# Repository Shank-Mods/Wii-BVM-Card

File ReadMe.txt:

These are the files I used to create the RVL-129X, a Wii on a BVM card. It is based on Martin's card. This project is essentially me craming his circuit into the corner, and adding pads to 1: solder the controller ports to and 2: bolt the Wii on. Consult his github for more info on the capabilities of the card portion of this project, as well as the software to program the Arduino.

Major Credits to Martin. Heres his github. He was awesome and super helpful. Could not have done this without him. Again, I just copied his homework and bolted a Wii to it. 
https://github.com/skumlos/bkm-129x-simple

It was a quick and dirty project not originally intended for public release. I am releaseing the files as is due to popular demand. It is cluttered, unoptimized, and made for my specific circumstances and my available parts. Sorry in advance.

Follow the Definitive Wii trimming gudie for information on how to trim and run the Wii. Standard trim. Run YPbPr and audio through shielded wire to the marked pads. SH is ground for shielding. Connect Controller lines to controller pads. 4 Layer Wii highly recommended. Leave the 1.8v LDO on the Wii. Ensure your Wii's settings have the resolution set to 480i if your PVMs are 15khz only. If your system is in 480p mode, you can disconnect the 3.3v-to-mode connection so set the system to composite and svideo mode, and run composite or luma to the Y line on the card for a usable black and white 15khz image that will let you navigate menus. 

The 129x card cannot pass audio through the slot, so audio comes out a 3.5mm jack and into the RCA jacks on the back. 

For voltage regulators, I purchased and bolted on an RVL-PSU. It contains all the voltage regulator rails the Wii needs. It is open source. You can assemble one yourself, use the open source design to integrate it onto this PCB, buy an RVL-PSU from CrazyGadget on the Bitbuilt forums, or design your own regulators if you are a pro. Do not use generic chinese voltage regulator boards, their power is not clean and will cause issues.

I included overkill voltage protection for every voltage rail of every controller port. This is because I plan to take it to Melee tournaments. The competitive Melee conroller modding scene has a huge problem with design and quality control of aftermarket and modded controllers. Many systems at tournaments have destroyed components caused by controllers overdrawing the voltage rails. These components are overkill, expensive, and tedious to solder. If these circumstances are not relevant to you, you can omit these components placed by the controller ports, and instead run 3.3v and 5v directly to the 3.3v and 5v pins of the controller ports with wires. 

Near the solder pads for the gamecube controller data wires are some diodes and filters. These are harvested from the lines connected to the data lines on the Wii motherboard. Diodes are for extra ESD protection. Filters can probably be jumpered over, but probably not best practice.

Resistors R2, R3, R4 and R5, along with R14, R15, R16 and R17 are not populated on this board. Csync pad is not used.

For screws I used the silver screws inside the wii, used mostly on the EMI shield.

For the fan and heatsink my usual setup: 35mm x 35mm x 7mm fan with 35mm x 35mm x 7mm heatsink, along with a 35x70mm copper plate. This setup has become the go-to in the portablizing community, and is used on many portables like the G-Wii. Use thermal paste between heatsink and copper plate. Use thermal pad between CPU/GPU and copper plate.

I didnt really plan where to put the USB port. I used a USB to micro SD card adapter, and mounted it to a GCC controller port with double sided foam adhesive tape. 

Theres an LDO (U5) that I didn't include on BOM because the replacement I purchased had a different pinout. I had to bodge it, but I added a jumper in case your LDO has that pinout. Check his github for specs on that part.

Included are 2 STLs that need to be printed. One is for mounting the Wii and the cooling system to the board. The other is the back plate. The back plate has 2 versions. V2 is the one I used. The extrusions for the screws are a little flimsy, so i made V3 to strengthen them. It should work and be stronger, but I never tested it so I included both. All 3d printed parts are mounted with silver scews from the Wii.

Order PCB with 1.6mm thickness. Its a 2 layer board, nothing special.

If you use this project, please credit me. Would love to see what people make with this. If you plan to monetize, please contact me.  

Troubleshooting tips I wish I knew:

Arduino must be programmed using the header. It WILL NOT WORK if programmed through the USB port on the arduino. 

Make sure U2 is being powered by U5 regulator. Different LDOs in that package have different pinouts. 

You can troubleshoot the signal chain by taking the Luma signal and skipping U2 and U1

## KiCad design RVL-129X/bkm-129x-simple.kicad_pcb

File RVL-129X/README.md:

A simplified version of the BKM-129X compatible board.

Should be able to be created at $25-30, with the ADG1611 being the most expensive component.

This requires an Arduino Nano v3 loaded with the latest BKM-129X-MCU code from https://github.com/skumlos/bkm-129x-mcu

For more information go to https://immerhax.com/?p=422

You are welcome to clone, produce and sell hardware based on this. Please keep changes and so on open source.

Cool kids give credit where due.

Thanks goes out to Nick Carney and Bob from RetroRGB for rigorious testing!

--------

Compatibility list and tested consoles (including issues):

PVM-9L2
- SNES (US region, CSYNC)
- Mega Drive 2 (EU region, 60 Hz modded with DFO for "true" 60 Hz, CSYNC)
- Master System 1 (EU region, 60 Hz modded with DFO for "true" 60 Hz, CSYNC)
- PC-Engine (White, with THS7374 external RGB amp, CSYNC)

BVM-D14
- Genesis 1 (60 Hz, CSYNC)

BVM-D9
- Nomad (60 Hz, Triple bypass modded, CSYNC)
- SNES (US region, CSYNC)
- Master System (60 Hz, sync issues like original 129X)
- TurboGrafx/PC-Engine (60 Hz, sync issues like original 129X)

---------

Board revision history:

D: Fix THS7374 filter bypass, move to Kicad 5

C: Rearranged some components for nicer layout

B: Added R29, R30, R31 to compensate for overbrightness

A: Changed R9 to 0 Ohm / jumper

---------

Copyright © 2020 Martin Hejnfelt <martin@hejnfelt.com>
This work is free. You can redistribute it and/or modify it under the
terms of the Do What The Fuck You Want To Public License, Version 2,
as published by Sam Hocevar. See the LICENSE file for more details.

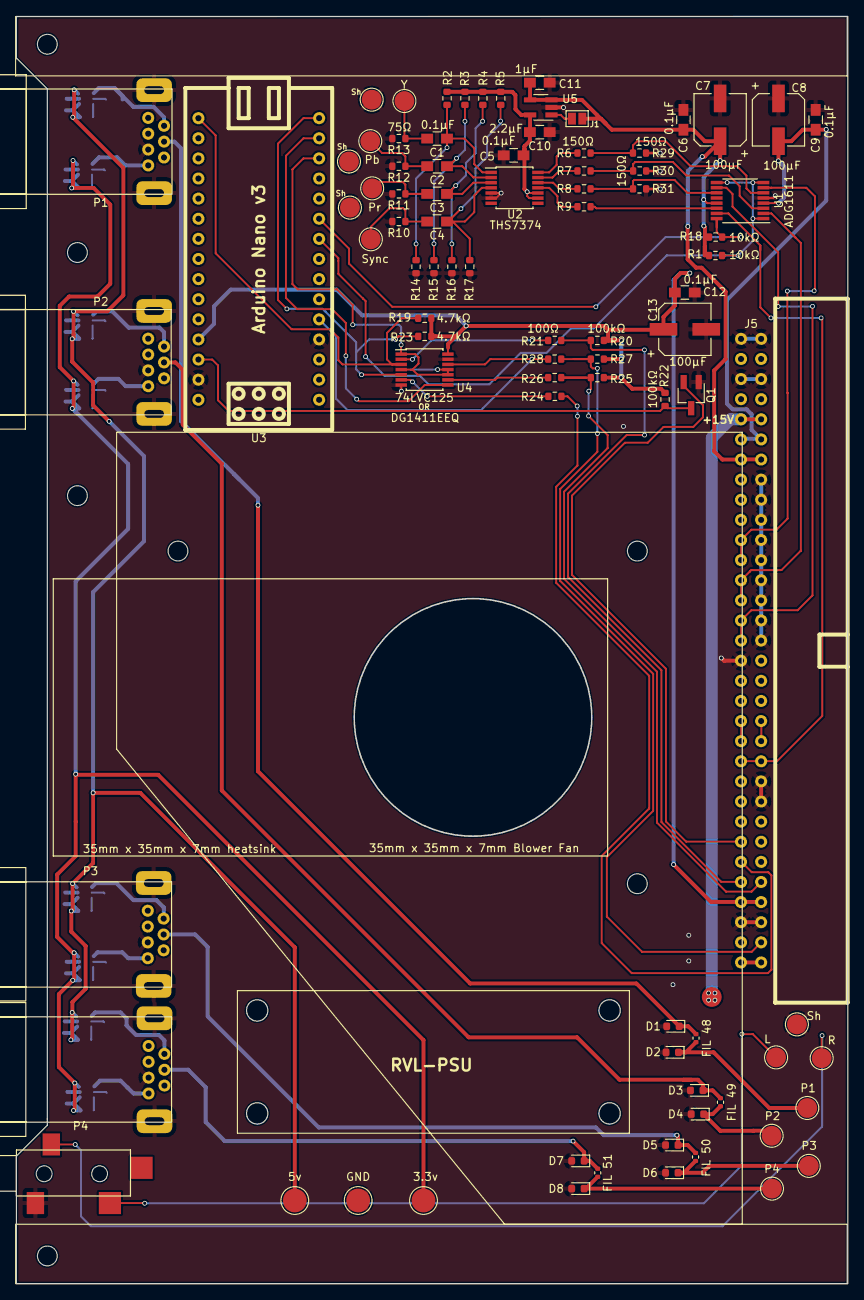
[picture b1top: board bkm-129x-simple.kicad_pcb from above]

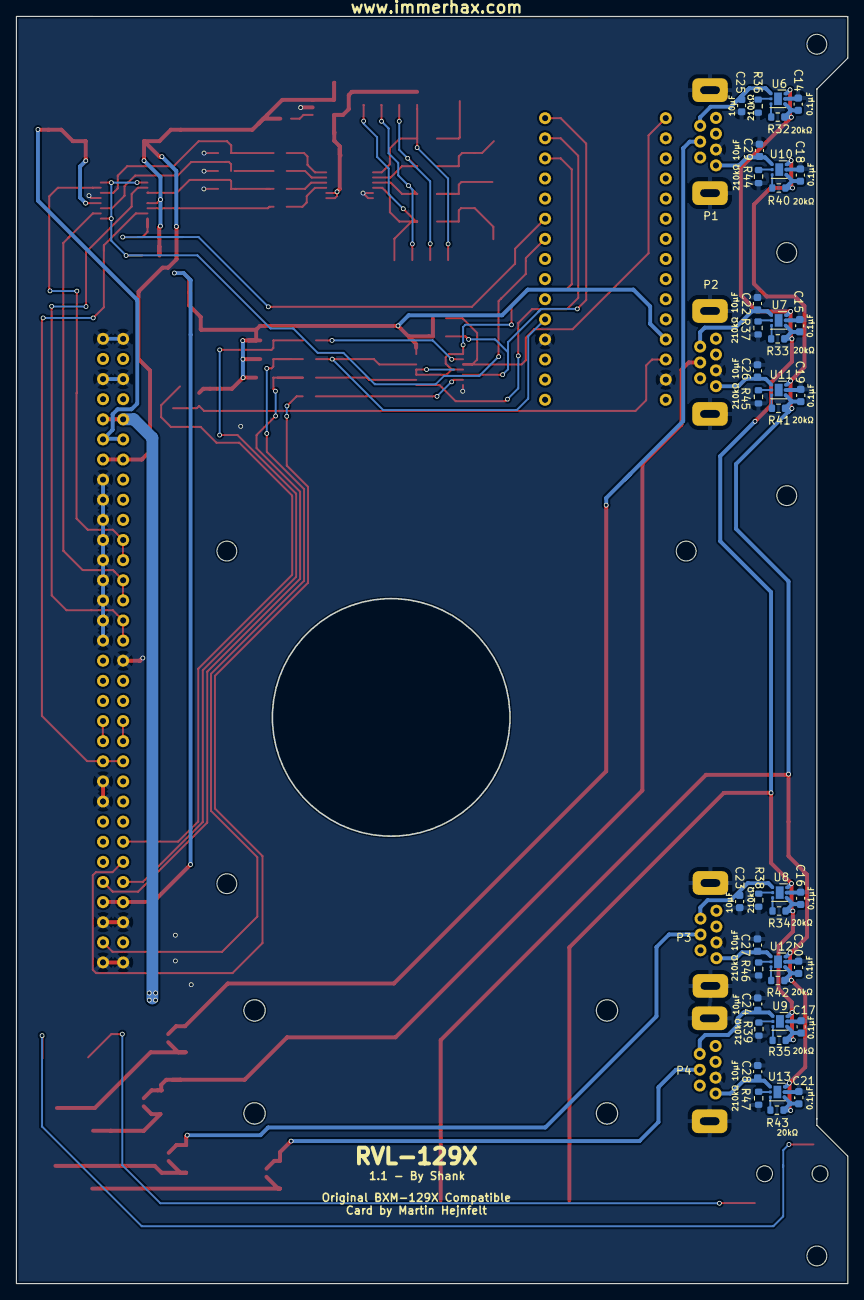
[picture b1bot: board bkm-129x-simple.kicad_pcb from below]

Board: 2 copper layers, 105.0 x 160.0 mm, 124 parts (40 on the bottom side), 71 nets.

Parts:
C1, C2, C3, C4, C5, C6, C9, C12: 0.1uF; C_0805_HandSoldering
C7, C8, C13: 100uF; CP_Elec_6.3x5.3
C10: 2.2uF; C_0805_HandSoldering
C11: 1uF; C_0805_HandSoldering
C14, C15, C16, C17, C18, C19, C20, C21, C22, C23, C24, C25, C26, C27, C28, C29: C; C_0603_1608Metric
CN1, CN2: GC_Ports; GCC Ports
D1, D2, D3, D4, D5, D6, D7, D8: D; D_0603_1608Metric
J1: SolderJumper-2_P1.3mm_Open_Pad1.0x1.5mm
J5: Conn_02x32_Row_Letter_Last; DIN-41612-64P
Q1: DTC144EKA; SC-59_Handsoldering
R1, R18: 10K; R_0603_1608Metric
R2, R3, R4, R5, R14, R15, R16, R17, R32, R33, R34, R35, R36, R37, R38, R39, R40, R41, R42, R43, R44, R45, R46, R47: R; R_0603_1608Metric
R6, R7, R8, R29, R30, R31: 150R; R_0603_1608Metric
R9: 0R; R_0603_1608Metric
R10, R11, R12, R13: 75R; R_0603_1608Metric
R19, R23: 4K7; R_0603_1608Metric
R20, R22, R25, R27: 100K; R_0603_1608Metric
R21, R24, R26, R28: 100R; R_0603_1608Metric
R48, R49, R50, R51: R; R_0402_1005Metric
TP1, TP2, TP3: TestPoint; TestPoint_Pad_D3.0mm
TP4, TP5, TP6, TP7, TP8, TP9, TP10, TP11, TP12, TP13, TP14, TP15, TP16, TP17: TestPoint; TestPoint_Pad_D2.5mm
U1: ADG1611; TSSOP-16_4.4x5mm_Pitch0.65mm
U2: THS7374; TSSOP-14_4.4x5mm_Pitch0.65mm
U3: arduino-nano-v3
U4: 74LVC125; TSSOP-14_4.4x5mm_Pitch0.65mm
U5: MIC3490-3.3; SOT-23-5_HandSoldering
U6, U7, U8, U9, U10, U11, U12, U13: TPS25221; WSON-6-1EP_2x2mm_P0.65mm_EP1x1.6mm
U14: PWP2_HeadphoneJackWithSwitch; HPJack

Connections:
3V3-P1: C29.1, CN1.7A (3.3v), U10.1 (OUT)
3V3-P2: C26.1, CN1.7B (3.3v), U11.1 (OUT)
3V3-P3: C27.1, CN2.7A (3.3v), U12.1 (OUT)
3V3-P4: C28.1, CN2.7B (3.3v), U13.1 (OUT)
3V3-PSU: C18.1, C19.1, C20.1, C21.1, R40.2, R41.2, R42.2, R43.2, TP1.1, U10.4 (EN), U10.6 (IN), U11.4 (EN), U11.6 (IN), U12.4 (EN), U12.6 (IN), U13.4 (EN), U13.6 (IN)
5V-P1: C25.1, CN1.1A (5v), U6.1 (OUT)
5V-P2: C22.1, CN1.1B (5v), U7.1 (OUT)
5V-P3: C23.1, CN2.1A (5v), U8.1 (OUT)
5V-P4: C24.1, CN2.1B (5v), U9.1 (OUT)
5V-PSU: C14.1, C15.1, C16.1, C17.1, R32.2, R33.2, R34.2, R35.2, TP2.1, U6.4 (EN), U6.6 (IN), U7.4 (EN), U7.6 (IN), U8.4 (EN), U8.6 (IN), U9.4 (EN), U9.6 (IN)
+3V3: C5.1, C10.1, R2.1, R3.1, R4.1, R5.1, U2.9 (BYPASS), U2.10 (VCC), U5.5 (VOUT)
+5VD: C12.1, C13.1, R19.2, R20.2, R22.1, R23.2, R25.2, R27.2, U3.27 (5V), U4.14 (VCC)
/MCU_SCK: R19.1, U3.16 (17/PB5/PCINT5/SCK), U4.3 (O)
/MCU_SLOT_ID: R28.1, U3.5 (32/PD2/INT0/PCINT18), U4.12 (D)
/MOSI: R25.1, R26.2
/SCLK: R20.1, R21.2
/SLOT_ID: R27.1, R28.2
/~MCU_RESET: Q1.3 (C), R22.2, U3.28 (29/PC6/RST/PCINT14)
GCC-P1: CN1.2A (DA), D1.1 (K), R48.2
GCC-P1-Pad: D2.1 (K), R48.1, TP4.1
GCC-P2: CN1.2B (DA), D3.1 (K), R49.2
GCC-P2-Pad: D4.1 (K), R49.1, TP5.1
GCC-P3: CN2.2A (DA), D5.1 (K), R50.2
GCC-P3-Pad: D6.1 (K), R50.1, TP6.1
GCC-P4: CN2.2B (DA), D7.1 (K), R51.2
GCC-P4-Pad: D8.1 (K), R51.1, TP7.1
GND-PSU: C5.2, C6.2, C7.2, C8.1, C9.2, C10.2, C11.1, C12.2, C13.2, C14.2, C15.2, C16.2, C17.2, C18.2, C19.2, C20.2, C21.2, C22.2, C23.2, C24.2, C25.2, C26.2, C27.2, C28.2, C29.2, CN1.6A (GND), CN1.6B (GND), CN1.8 (Shield), CN2.6A (GND), CN2.6B (GND), CN2.8 (Shield), D1.2 (A), D2.2 (A), D3.2 (A), D4.2 (A), D5.2 (A), D6.2 (A), D7.2 (A), D8.2 (A), J5.1a, J5.1b, J5.3a, J5.3b, J5.8a, J5.9a, J5.10a, J5.11a, J5.12a, J5.13a, J5.14a, J5.15a, J5.16a, J5.17b, J5.23a, J5.24a, J5.30a, J5.30b, J5.32a, J5.32b, Q1.1 (E), R10.2, R11.2, R12.2, R13.2, R14.2, R15.2, R16.2, R17.2, R29.2, R30.2, R31.2, R36.2, R37.2, R38.2, R39.2, R44.2, R45.2, R46.2, R47.2, TP3.1, TP8.1, TP9.1, TP10.1, TP11.1, U1.5 (GND), U2.5 (GND), U2.6 (DISABLE), U3.4 (GND), U3.29 (GND), U4.7 (GND), U4.13 (E), U5.2 (GND), U6.5 (GND), U7.5 (GND), U8.5 (GND), U9.5 (GND), U10.5 (GND), U11.5 (GND), U12.5 (GND), U13.5 (GND), U14.1 (Sleeve/Shield)
unnamed: C1.1, R2.2, R14.1, U2.1 (CH1_IN)
unnamed: C1.2, R13.1, TP12.1
unnamed: C2.1, R3.2, R15.1, U2.2 (CH2_IN)
unnamed: C2.2, R12.1, TP13.1
unnamed: C3.1, R4.2, R16.1, U2.3 (CH3_IN)
unnamed: C3.2, R11.1, TP14.1
unnamed: C4.1, R5.2, R17.1, U2.4 (CH4_IN)
unnamed: C4.2, R10.1, TP15.1
unnamed: R6.2, U2.14 (CH1_OUT)
unnamed: R7.2, U2.13 (CH2_OUT)
unnamed: R8.2, U2.12 (CH3_OUT)
unnamed: R9.1, U1.14 (S)
unnamed: R9.2, U2.11 (CH4_OUT)
unnamed: R21.1, U4.2 (D)
unnamed: R23.1, U3.15 (16/PB4/PCINT4/MISO), U4.5 (D)
unnamed: R24.1, U4.6 (O)
unnamed: R26.1, U4.9 (D)
unnamed: R6.1, R29.1, U1.6 (S)
unnamed: R7.1, R30.1, U1.3 (S)
unnamed: R8.1, R31.1, U1.11 (S)
unnamed: R32.1, U6.3 (FAULT)
unnamed: R33.1, U7.3 (FAULT)
unnamed: R34.1, U8.3 (FAULT)
unnamed: R35.1, U9.3 (FAULT)
unnamed: R36.1, U6.2 (ILIM)
unnamed: R37.1, U7.2 (ILIM)
unnamed: R38.1, U8.2 (ILIM)
unnamed: R39.1, U9.2 (ILIM)
unnamed: R40.1, U10.3 (FAULT)
unnamed: R41.1, U11.3 (FAULT)
unnamed: R43.1, U13.3 (FAULT)
unnamed: R44.1, U10.2 (ILIM)
unnamed: R45.1, U11.2 (ILIM)
unnamed: R46.1, U12.2 (ILIM)
unnamed: R47.1, U13.2 (ILIM)
unnamed: TP16.1, U14.2 (Tip/Left)
unnamed: TP17.1, U14.3 (Ring/Right)
unnamed: U3.13 (14/PB2/OC1B/PCINT2/~SS), U4.1 (E), U4.4 (E), U4.10 (E), U4.11 (O)
unnamed: U3.14 (15/PB3/OC2/PCINT3/MOSI), U4.8 (O)
unnamed: R42.1, U12.3 (FAULT)
VDD: C6.1, C7.1, C11.2, J1.2, J5.7a, J5.7b, R1.2, R18.1, U1.13 (VDD), U5.3 (EN), U5.4 (VIN)
VSS: C8.2, C9.1, J5.6a, J5.6b, U1.4 (VSS)
~BX_OE: R1.1, U1.1 (IN), U1.8 (IN), U1.9 (IN), U3.9 (10/PD6/AIN0/PCINT22/OC0A)
~EXT_SYNC_OE: R18.2, U1.16 (IN), U3.10 (11/PD7/AIN1/PCINT23)

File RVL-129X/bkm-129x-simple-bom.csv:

Id,Designator,Package,Quantity,Designation,Supplier;and;ref;;;;;;;;;;;
"1,""C1,C2,C3,C4,C5,C6,C9,C12"",C_0805_HandSoldering,8,0.1uF,";;;;;;;;;;;;;
"2,""C7,C8,C13"",CP_Elec_6.3x5.3,3,100uF,";;;;;;;;;;;;;
3,J1,BNC-THT,1,YG1,ADAM;TECH;RF1-01B-D-00-75;(but;others;are;compatible);;;;;;;
4,J2,BNC-THT,1,PBB1,ADAM;TECH;RF1-01B-D-00-75;(but;others;are;compatible);;;;;;;
5,J3,BNC-THT,1,PRR1,ADAM;TECH;RF1-01B-D-00-75;(but;others;are;compatible);;;;;;;
6,J4,BNC-THT,1,SYNC1,ADAM;TECH;RF1-01B-D-00-75;(but;others;are;compatible);;;;;;;
7,J5,DIN-41612-64P,1,Conn_02x32_Row_Letter_Last,Amphenol;T821-1-64-R1;(but;any;64-pin;(2x32);pin;header;with;2.54;mm;pitch;seems;good)
8,Q1,SC-59_Handsoldering,1,DTC144EKA,;;;;;;;;;;;;;
"9,""R1,R18"",R_0805_HandSoldering,2,10K,";;;;;;;;;;;;;
"10,""R2,R3,R4,R5,R14,R15,R16,R17"",R_0805_HandSoldering,8,R,";;;;;;;;;;;;;
"11,""R6,R7,R8,R29,R30,R31"",R_0805_HandSoldering,6,150R,";;;;;;;;;;;;;
12,R9,R_0805_HandSoldering,1,0R,;;;;;;;;;;;;;
"13,""R10,R11,R12,R13"",R_0805_HandSoldering,4,75R,";;;;;;;;;;;;;
"14,""R20,R22,R25,R27"",R_0805_HandSoldering,4,100K,";;;;;;;;;;;;;
"15,""R21,R24,R26,R28"",R_0805_HandSoldering,4,100R,";;;;;;;;;;;;;
"16,""R23,R19"",R_0805_HandSoldering,2,4K7,";;;;;;;;;;;;;
17,U1,TSSOP-16_4.4x5mm_Pitch0.65mm,1,ADG1611,;;;;;;;;;;;;;
18,U3,arduino-nano-v3,1,arduino-nano-v3,;;;;;;;;;;;;;
19,U2,TSSOP-14_4.4x5mm_Pitch0.65mm,1,THS7374,;;;;;;;;;;;;;
20,U4,TSSOP-14_4.4x5mm_Pitch0.65mm,1,74VHC125,Note;74VHC125;;;;;;;;;;;;
21,C10,C_0805_HandSoldering,1,2.2uF,;;;;;;;;;;;;;
22,C11,C_0805_HandSoldering,1,1uF,;;;;;;;;;;;;;
23,U5,SOT-23-5_HandSoldering,1,MIC3490-3.3,;;;;;;;;;;;;;

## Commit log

2023-03-03 Update ReadMe.txt
    Clarified text regarding setting 15khz on the Wii.
